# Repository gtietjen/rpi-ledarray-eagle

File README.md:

# rpi-ledarray-eagle

## Description

<p>The RPi LED array is a printed circuit board that mates directly with the GPIO (general purpose input/output) headers of a Raspberry Pi computer. This module adds a 10 LED array that can be controlled by software however you'd like. The Raspberry Pi GPIO can be accessed and controlled by many different languages, and code examples can be found at: http://elinux.org/Rpi_Low-level_peripherals#GPIO_Code_examples</p>
<p>The LEDs are connected to the GPIO headers with their anode to the 5V pins and their cathode to a controllable GPIO pin via a current limiting series resistor. There are many reasons why they are connected this way. The first reason being the power supply. The GPIO pins provide both a 3.3V source and a 5V source. The 5V source is from the board's 5V power supply and is limited mostly by the power adapter being used. The 3.3V supply pins can only supply about 50mA. With 10 LEDs on the array board, 50mA simply isn't enough current, especially if you'd like to turn all LEDs on. All the numbered GPIO pins are 3.3V levels and can only source a maximum of 50mA, however they are able to sink up to 16mA per pin. So, each LED is being supplied 5V and being sinked to ground by a 3.3V level GPIO pin on command.</p>
<p>Since each LED is being supplied with 5V and sinked to ground, this alters the logic behind controlling each LED. To turn an LED on, a GPIO pin must be pulled to ground, LOW or 0 state. To turn an LED off completely, a GPIO pin was must be placed in an INPUT state, i.e. Hi-Z or high impedance state. You can turn an LED off by pulling the GPIO pin to a logic level HIGH or 1 state, but you may notice the LED is not completely off.</p>

## Dimensions
The board is approximately 1.31" x 0.62". The board has been designed to fit within a [Pibow](http://shop.pimoroni.com/products/pibow) Raspberry Pi case by [Pimoroni](http://shop.pimoroni.com/).

## LED Mapping
| LED | GPIO Pin |
|:---:|:--------:|
| 1 | 4 |
| 2 | 17 |
| 3 | 27 |
| 4 | 22 |
| 5 | 18 |
| 6 | 23 |
| 7 | 24 |
| 8 | 25 |
| 9 | 8 |
| 10 | 7 |

## Bill of Materials

| Part Number(s)	| Description	| Manufacturer	| MFG Number	| Distributor |
| ------------------|:-------------:| :------------:|:-------------:|:------------:|
| R1, R2, R3, R4, R5, R6, R7, R8, R9, R10 | RES 220 OHM 1/10W 5% 0603 SMD | Yageo | RC0603JR-07220RL | <a href="http://www.digikey.com">Digikey</a> |
| LED1, LED2, LED3, LED4, LED5, LED6, LED7, LED8, LED9, LED10 | LED 3X1.5MM 568NM GN WTR CLR SMD | Kingbright | APL3015SGC-F01 | <a href="http://www.digikey.com">Digikey</a> |
| JP1 | CONN HEADER FMAL 26PS .1" DL TIN | Sullins Connector Solutions | PPTC132LFBN-RC | <a href="http://www.digikey.com">Digikey</a> |

## Testing the board

In the "code" folder is a Bash script for testing the LED array PCB. In a terminal window on the Raspberry Pi, navigate to the "code" folder and run the following command:

	sudo bash testLEDarray.sh

-OR-

	sudo ./testLEDarray.sh

While the script is running, the LEDs on the LED array PCB should illuminate one by one in sequential order until all LEDs are illuminated. All LEDs should then turn off.

## Images

## Additional Scripts

In the "code" folder exists a variety of scrips that make use of the Raspberry Pi LED array:

<i>showDiskUsage.sh</i> - Displays the Raspberry Pi's disk usage

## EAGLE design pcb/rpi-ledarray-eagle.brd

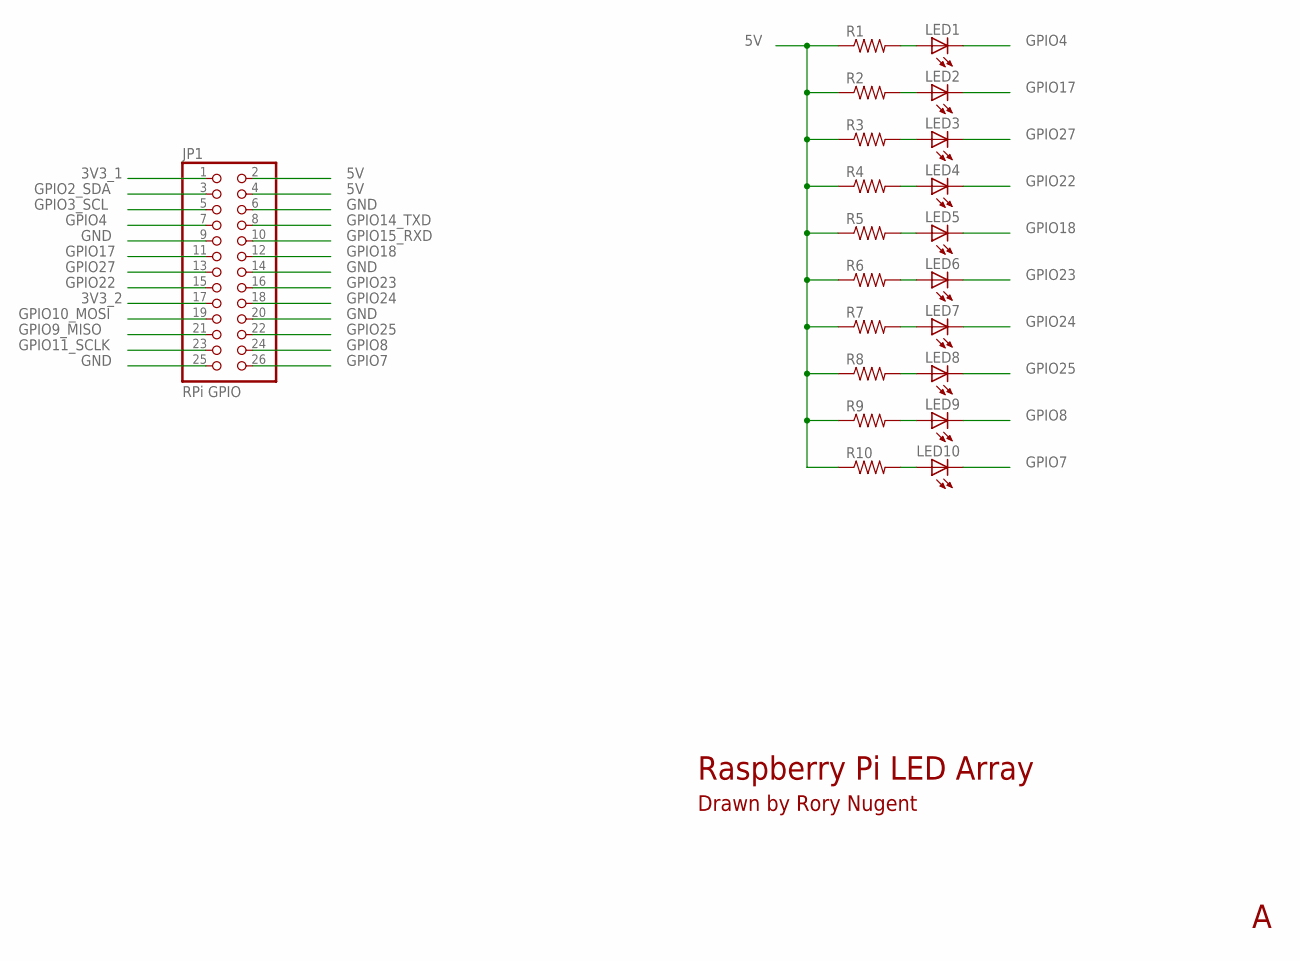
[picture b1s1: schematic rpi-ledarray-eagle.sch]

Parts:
JP1: RPi GPIO; 2X13
LED1, LED2, LED3, LED4, LED5, LED6, LED7, LED8, LED9, LED10: LED1206; LED-1206
R1, R2, R3, R4, R5, R6, R7, R8, R9, R10: RESISTOR0603-RES; 0603-RES

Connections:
3V3_1: JP1.1
3V3_2: JP1.17
5V: JP1.2, JP1.4, R1.1, R2.1, R3.1, R4.1, R5.1, R6.1, R7.1, R8.1, R9.1, R10.1
GND: JP1.6, JP1.9, JP1.14, JP1.20, JP1.25
GPIO2_SDA: JP1.3
GPIO3_SCL: JP1.5
GPIO4: JP1.7, LED1.C
GPIO7: JP1.26, LED10.C
GPIO8: JP1.24, LED9.C
GPIO9_MISO: JP1.21
GPIO10_MOSI: JP1.19
GPIO11_SCLK: JP1.23
GPIO14_TXD: JP1.8
GPIO15_RXD: JP1.10
GPIO17: JP1.11, LED2.C
GPIO18: JP1.12, LED5.C
GPIO22: JP1.15, LED4.C
GPIO23: JP1.16, LED6.C
GPIO24: JP1.18, LED7.C
GPIO25: JP1.22, LED8.C
GPIO27: JP1.13, LED3.C
unnamed: LED1.A, R1.2
unnamed: LED3.A, R3.2
unnamed: LED2.A, R2.2
unnamed: LED4.A, R4.2
unnamed: LED10.A, R10.2
unnamed: LED9.A, R9.2
unnamed: LED8.A, R8.2
unnamed: LED7.A, R7.2
unnamed: LED6.A, R6.2
unnamed: LED5.A, R5.2

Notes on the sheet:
Drawn by Rory Nugent
Raspberry Pi LED Array

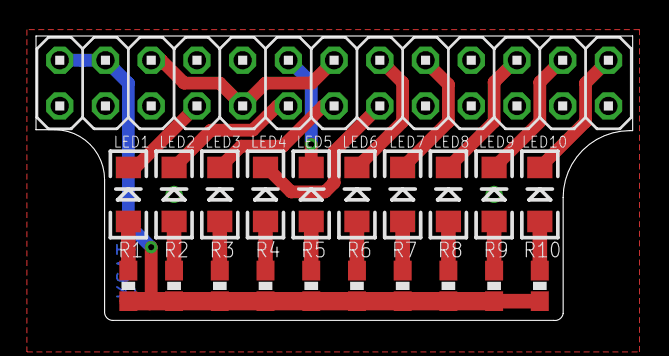
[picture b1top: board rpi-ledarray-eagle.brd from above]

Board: 2 copper layers, 33.1 x 15.8 mm, 22 parts (1 on the bottom side), 22 nets.

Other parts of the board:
U$2: OSHW_FILLX200_NOTEXT

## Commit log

2013-05-14 First version finished
2013-05-30 Adjusted board dimensions. Adjusted font size and placement.
2013-05-31 Changed resistors to 0603. Shrunk the board dimensions.
2013-05-31 Moved the drill holes slightly.
2013-06-25 Added OSHW logo. Added rev number on the bottom copper. Increased resistor silk label size.
2013-06-25 Adding BOM to the README
2013-06-26 Added tester bash script. Moved files to folders. Added some script instructions to the README.
2013-06-26 Updated schematic so the LEDs were in sequential order. Very minor README update.
2013-06-26 Updated the README. Added measurements to the Eagle board.
2013-06-26 Minor README corrections.
2013-06-28 Added images
2013-06-28 Updating readme
2013-08-20 Working on script to show used disk space on the LED array
2013-08-27 Mention the disk usage script in the README. Minor change to the test script to turn off all LEDs on start.
2013-08-27 Italicized mention of ShowDiskUsage.sh

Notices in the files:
parts and their libraries:
SparkFun: Licensing: CC v3.0 Share-Alike You are welcome to use this library for commercial purposes.
